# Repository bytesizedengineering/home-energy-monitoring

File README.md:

# Whole-Home Energy Monitoring System

*A DIY, ESP32-based energy monitoring system that tracks up to 9 circuits using CT clamps and integrates seamlessly with Home Assistant.* 

## 🚀 Overview  
This project provides a cost-effective way to monitor real-time electricity usage across multiple circuits in your home. By using non-invasive Current Transformer (CT) clamps, the system measures magnetic induction to calculate amperage without cutting into your home's wiring.

This project was featured on the [DigiKey YouTube channel](https://www.youtube.com/@digikey) in [this video](https://youtu.be/54pZV8P7hGM?si=jUmZ82UDNDB7HiG6).

## 📂 Repository Structure  
```
📁 mechanical design/   # 3D printable enclosure files (STLs, STEP)
📁 electrical design/   # KiCad PCB files for the stackable 3-channel CT board
📁 firmware/            # ESPHome YAML configuration files
📁 docs/                # Documentation
```

## 🏗️ Build Instructions  

### 🔌 Electronics  
The hardware is built around a stackable PCB design that can scale up to nine individual channels.
- **Microcontroller**: Seeed Studio XIAO ESP32-S3.
- **Sensors**: SCT-013-000 Current Transformer (CT) clamps.
- **PCB Fabrication**: The board uses 3.5mm TRS audio jacks for sensor connections.

### 💾 Firmware Upload  
The system uses **ESPHome** for easy integration with Home Assistant.
1. Install the [ESPHome dashboard](https://esphome.io/).
2. Connect your XIAO ESP32-S3 via USB-C.
3. Add a new ESPHome device, and create a New Device Setup yaml file. This will create entries for api, wifi, and ota. Make sure you've already setup a SECRETS file to store your wifi credentials. 
4. Open the provided `.yaml` configuration in the `firmware/` folder. Copy everything starting with captive portal: and paste into the yaml created in the previous step. This ensures your device has a new and unique api and ota entries. Don't use the ones included in the yaml file
5. Click install to compile a binary. Save the binary locally and use ESPHome web to flash the device. After this first flash, the device can be updated over the air (OTA) wirelessly. 
6. Add the device to your **Home Assistant** instance via the Integrations page.

## 🛒 Bill of Materials (BOM)  
| Part             | Description                                    | Purchase Link                                     |
| ---------------- | ---------------------------------------------- | ------------------------------------------------- |
| Microcontroller  | Seeed Studio XIAO ESP32-S3                     | [DigiKey](https://www.digikey.com/en/products/detail/seeed-technology-co-ltd/113991114/19285530?s=N4IgTCBcDaIIwFYCcB2AtHOBmJTNwBY0A5AERAF0BfIA)                |
| CT Clamps        | SCT-013-000 (100A/50mA)                        | [DigiKey](https://www.digikey.com/en/products/detail/seeed-technology-co-ltd/101990029/5488226)                |
| Burden Resistor  | 20 Ohm (for 3.3V ADC compatibility)            | [DigiKey](https://www.digikey.com/en/products/detail/stackpole-electronics-inc/RNCP0603FTD20R0/2240076?s=N4IgTCBcDaIEoDkDCAFADANjQZgGIBUARMNONJfAWgUJAF0BfIA)                |
| Voltage Divider  | 100K Ohm Resistors (x2 per channel)            | [DigiKey](https://www.digikey.com)                |
| Filter Capacitor | 10uF Electrolytic Capacitor                    | [DigiKey](https://www.digikey.com)                |
| Connectors       | 3.5mm TRS Audio Jacks (PCB Mount)              | [DigiKey](https://www.digikey.com/en/products/detail/same-sky-formerly-cui-devices/SJ-3523-SMT-TR/281297?s=N4IgTCBcDaIMIAUC0BmArGFBlAUnAKkgHIAiIAugL5A)                |

## 🎥 Video & More Info  
📺 Watch the full build and calibration process: [YouTube Video](https://youtu.be/54pZV8P7hGM?si=jUmZ82UDNDB7HiG6)  
📄 Read the technical breakdown: [Article on Maker.io](https://www.digikey.com/en/maker/projects/build-a-diy-whole-home-energy-monitor-with-esphome-and-home-assistant/be84610c06894f87a0f75bd443de7992)

> [!CAUTION]
> **Safety Warning**: This project involves installing sensors inside a main utility panel. This should only be performed by individuals comfortable working around high voltage or a licensed electrician.

## 📝 License  
This project is licensed under the **GNU General Public License v3.0**.  

## ❤️ Support  
- Found this helpful? Consider supporting me on [Patreon](https://www.patreon.com/ByteSizedEngineering) or [YouTube Memberships](https://www.youtube.com/@ByteSizedEngineering/join).  
- Follow me on [YouTube](https://www.youtube.com/@ByteSizedEngineering), [Instagram](https://www.instagram.com/bytesizedengineering/), and [GitHub](https://github.com/bytesizedengineering).

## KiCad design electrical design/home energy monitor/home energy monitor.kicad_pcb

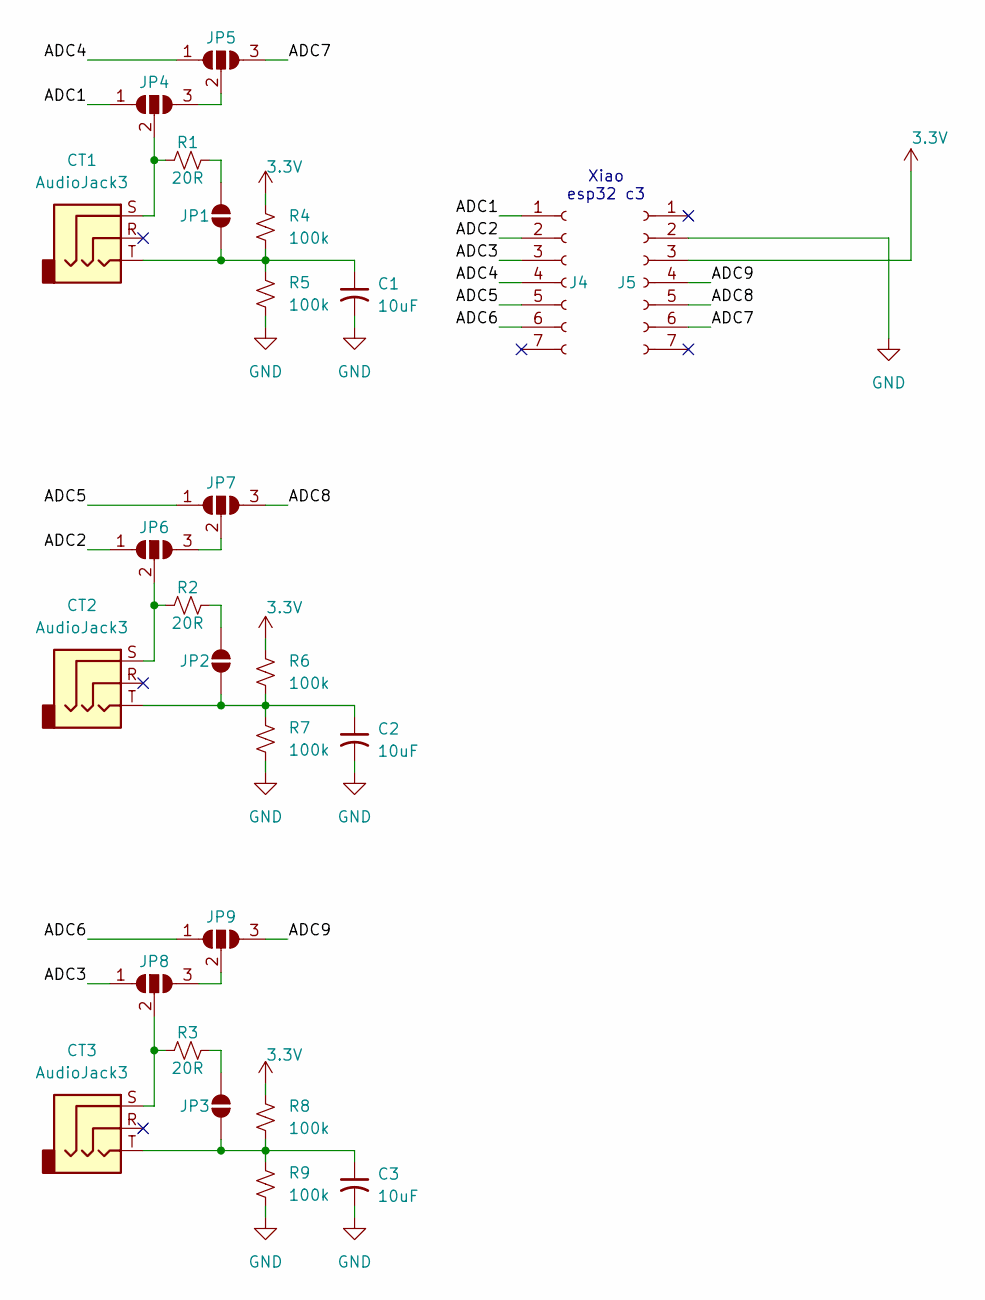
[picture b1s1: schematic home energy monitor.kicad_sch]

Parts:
C1, C2, C3: 10uF; C_0603_1608Metric_Pad1.08x0.95mm_HandSolder
CT1, CT2, CT3: AudioJack3; Jack_3.5mm_CUI_SJ-3523-SMT_Horizontal
J4, J5: Conn_01x07_Socket; PinSocket_1x07_P2.54mm_Vertical
JP1, JP2, JP3: burden resistor; SolderJumper-2_P1.3mm_Open_RoundedPad1.0x1.5mm
JP4, JP5, JP6, JP7, JP8, JP9: SolderJumper_3_Open; SolderJumper-3_P1.3mm_Open_RoundedPad1.0x1.5mm_NumberLabels
R1, R2, R3: 20R; R_0603_1608Metric_Pad0.98x0.95mm_HandSolder
R4, R5, R6, R7, R8, R9: 100k; R_0603_1608Metric_Pad0.98x0.95mm_HandSolder

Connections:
3.3V: J5.3, R4.1, R6.1, R8.1
/ADC1: J4.1, JP4.1 (A)
/ADC2: J4.2, JP6.1 (A)
/ADC3: J4.3, JP8.1 (A)
/ADC4: J4.4, JP5.1 (A)
/ADC5: J4.5, JP7.1 (A)
/ADC6: J4.6, JP9.1 (A)
/ADC7: J5.6, JP5.3 (B)
/ADC8: J5.5, JP7.3 (B)
/ADC9: J5.4, JP9.3 (B)
GND: C1.2, C2.2, C3.2, J5.2, R5.2, R7.2, R9.2
unnamed: C1.1, CT1.T, JP1.1 (A), R4.2, R5.1
unnamed: JP1.2 (B), R1.2
unnamed: C2.1, CT2.T, JP2.1 (A), R6.2, R7.1
unnamed: JP2.2 (B), R2.2
unnamed: C3.1, CT3.T, JP3.1 (A), R8.2, R9.1
unnamed: JP3.2 (B), R3.2
unnamed: JP4.3 (B), JP5.2 (C)
unnamed: CT1.S, JP4.2 (C), R1.1
unnamed: JP6.3 (B), JP7.2 (C)
unnamed: CT2.S, JP6.2 (C), R2.1
unnamed: JP8.3 (B), JP9.2 (C)
unnamed: CT3.S, JP8.2 (C), R3.1

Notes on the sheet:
Xiao esp32 c3

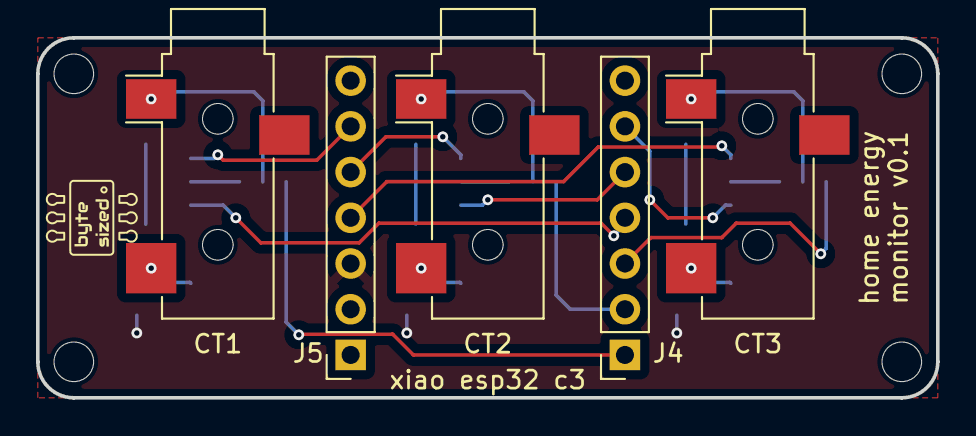
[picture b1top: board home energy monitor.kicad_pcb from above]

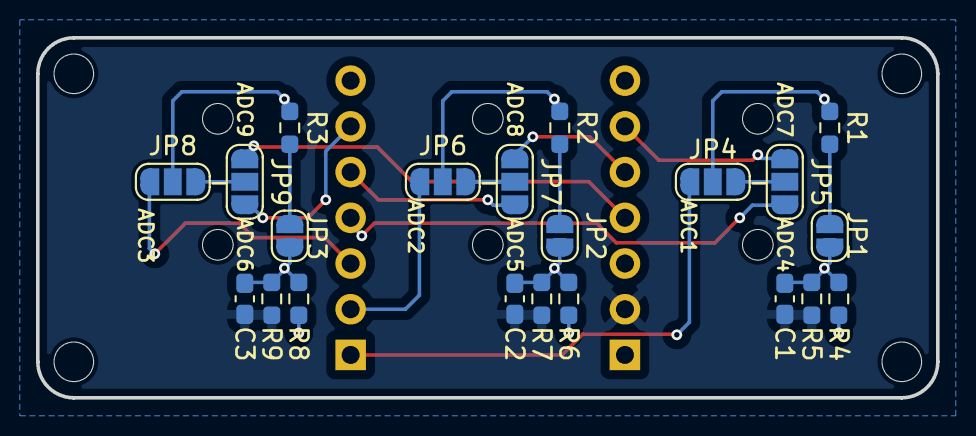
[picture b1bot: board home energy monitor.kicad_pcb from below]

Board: 2 copper layers, 50.0 x 20.0 mm, 26 parts (21 on the bottom side), 23 nets.

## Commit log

2026-05-23 Added PCB routing for alternate ADC pins
